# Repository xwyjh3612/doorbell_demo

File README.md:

# ESP32 4G 语音对讲

当前主板按A18外壳继续[两层语音对讲主板设计](hardware/voice_mainboard_v8_a18/README.md)，保留RGB指示灯、呼叫键、可选生命体征接口、4针TTL和USB预留。正在收尾的布线候选见[最新候选预览](hardware/voice_mainboard_v8_a18/routing_candidate/exports/preview.html)与[候选审查记录](hardware/voice_mainboard_v8_a18/routing_candidate/设计审查记录.md)；[其他工程预览入口](hardware/voice_mainboard_v8_a18/exports/preview.html)保留供比较。尚未生产放行，未连接、DRC和电源线宽以同版PCB的原生报告为准；V7及下文V6/V5费用保留为历史方案。四层工程保留作对照。

本项目是基于 ESP32-S3 + ML307 4G 的双向实时语音对讲系统。ESP32 使用 MQTT，安卓 App 和浏览器使用 WebSocket/WSS，`audio_server` Spring Boot 服务在两者之间转发 WebRTC 信令。双方通过 WebRTC/UDP/TURN 进行 Opus 16kHz 单声道语音对讲，信令服务不承载音频编解码。

独立安卓 App 支持呼叫、接听、拒接、挂断和麦克风控制，在线下载与现场操作见 [安卓演示说明.md](安卓演示说明.md)。演示入口：[https://voice.2811.top/demo.html](https://voice.2811.top/demo.html)。

0.9 版可在「设置 → 来电权限」开启后台弹窗。在其他 App 内也能看到来电页，通知与锁屏仍可直接接听。

0.8 版在首页和锁屏来电页显示动态听筒；呼出预警按日期呈现，可查看今天或近 7 天的记录。

0.7 版支持演示设备多手机接听：各手机安装并打开 App 即可同时收到来电。先接听的手机通话，其余手机停铃并显示接听者名称。设置中可把自动生成的本机名称改成“前台”或“调度室”。[呼出预警与并发呼叫说明](呼出预警与多路呼叫验证.md)

0.5版加入随无人、静止、活动变化的感知动效，以及按日期查看的状态时间线。历史由独立语音服务器保存30天，记录规则见[感知时间线与历史记录.md](感知时间线与历史记录.md)。同时移除App可恢复音频中断的8秒自动挂断，测试范围见[安卓音频恢复验证.md](安卓音频恢复验证.md)。

新增 [语音对讲 V6 集成 UPS 主板](hardware/voice_mainboard_v6/README.md)：真实充电、保护、升压与电源切换电路替换 V5 的接口预留，加入 ESP32 供电来源、电池电压和估算电量检测。新主板固件选项默认关闭，待机独立上报电源状态，App 已加入显示；[最新原生 PCB 预览与检查](hardware/voice_mainboard_v6/exports/review.html)如实列出剩余工作，尚未生产放行。以下 V5 价格与检查保留为历史方案，不能用于新 V6 下单。

当前降本设计见 [语音对讲V5主板](hardware/voice_mainboard_v5/README.md)：按用户确认的UPS输出稳压5V设计后级，ESP32-S3-WROOM-1-N8R8＋ML307C-DL直接贴板，100×75mm双层、单面SMT，圆口接5V/2A适配器。5V直接供I2S功放及可选雷达，分别降压给ESP32与4G模组，保留电量采样、BOOT接听及TTL四针。UPS内部芯片尚未确定，板上预留区域和六个焊线孔是电气接口，不能作为真实UPS芯片封装投产。本版材料＋UPS5元额度约44.09元，含PCB/加工/测试预算约52.59元/台；低价SIM座精确焊盘与器件验收完成后条件预算约50.69元/台。详见[当前逐项BOM和费用](hardware/voice_mainboard_v5/cost/费用说明.md)，均为1000台预算，非嘉立创工厂整单报价，不含电池和外设。[最新检查记录](hardware/voice_mainboard_v5/exports/validation.json)与实物验收边界随工程保存；尚未生产放行。此前[V4完整分立电源方案](hardware/voice_mainboard_v4/README.md)保留供对照。

此前的 [首批5台分阶段实施方案](首批5台分阶段实施方案.md)采用完整开发板和现有模块，先做直供电装盒演示，基础物料预算约565元。历史直供电预算不包含本轮集成主板设计。

硬约束仍是**基础语音款所有零件量产成本≤80元**。此前评估的[7元UPS模块及主板集成成本](7元UPS模块集成成本与80元整机目标.md)及100台4～6元电源目标不代表当前V3板的实际价格。V3选择了具体电源芯片并形成BOM，当前架构未达到80元目标；电量继续采用ESP32 ADC粗估，整机量产预算应包含电池、外壳、适配器等全部物料。

本轮[UPS板公开零件价格](7元UPS板公开零件价格核查.md)已列SL1045及同类电感/MOS/阻容的实际阶梯价。照片无法确认两颗主IC和完整BOM，因此尚无原板全物料公开成本合计；同类参考价格不直接作为原板替换采购料号。

完整产品需求、结构/PCB协同设计、软件运维和生产交付见 [从样机到小批销售和量产的完整路线](语音对讲产品从样机到量产路线.md)。开发板演示不能替代后续新PCB和批次工艺验证。

设备呼入使用双短电话铃，呼出使用回铃音；MQTT 联网后播放中文“联网成功”。音频素材与重新生成方法见 [提示音说明](main/call-tones.md)。

长期外接电源、偶尔断电由小电池接管的电源模块选型与接线见 [长期插电与备用电源](长期插电与备用电源.md)，包含 5V I2S 功放负载。

此前的四层模块版见 [语音对讲V3：ML307R-DL贴板与板载UPS](hardware/voice_mainboard_v3/README.md)。其[5/100/1000片费用](hardware/voice_mainboard_v3/cost/费用说明.md)及[可修改Excel](outputs/voice-v3-20261122/语音对讲V3主板费用.xlsx)保留为历史资料；1000片总成预算约125元/台包括外接开发板/模块，不是当前V5主板报价。V2/V3/V4及更早方案保留可追溯记录，后续降本以V5原生工程、实际BOM和新的1000台费用范围为依据。

本批现有手工样机的[40轮实机测试](tests/at_recovery_batch_20261121.md)已完成：33轮各自满半小时、7轮失败，电脑监督器中断1轮排除并补测；另在挂断阶段捕获ESP异常。官方协议、主动丢旧包策略及本批镜像未因PCB设计更改，旧样机结果不代表新板验收。

此前已画出 [可编辑原理图与PCB元件摆放草图](hardware/voice_carrier_v1/README.md)，保留可选生命体征雷达接口；PCB尚未布线，外壳及模块实物尺寸待核对。[带定制底板和备用电池的5台与100台预算](首版5台与100台成本.md)分别约1000元、1.39万元，属于后续候选配置，尚未取得完整供应商报价，不是当前直供电5台的采购预算。

后续评估定制备用电源底板时可参考 [此前采购与贴片清单、电路图和询价说明](outputs/first5-supplier/首批5台采购与商家询价.md)：底板每块42个SMT元件、13个插件，现有模块另外组装。当前5台直供电阶段不用这份底板BOM下单，后续设计与验证完成后再发布生产文件。

以现有约60元语音硬件为基准，备用小电池、电源管理、外壳和定制主板的增量预算，以及可选生命体征检测清单，参阅 [硬件清单与成本预算.md](硬件清单与成本预算.md)。

先用现有开发板制作带外壳和面板按钮的演示样机，选型、采购搜索入口及GPIO接线参阅 [演示样机外壳与按钮.md](演示样机外壳与按钮.md)。

## 协议约束

**ESP32 现有协议和官方 WebRTC/peer 组件保持不变。兼容转换在 Java 服务端完成。**

| 消息 | ESP32 上行字段 | ESP32 下行字段 | 浏览器常用字段 |
| --- | --- | --- | --- |
| `offer` / `answer` | `data` | `data` | `sdp` |
| `candidate` | `data` | `candidate` | `candidate` |
| `version_report` | `version` 为字符串 | — | 服务端转为整数 |
| `ota` | — | `url`、数字 `version`、可选 `md5` | 服务端配置 |

Java `SignalingMessage.normalizeMediaFields()` 补齐两种媒体字段，不改变设备使用的字段。因此默认 `index.html` 和 `index2.html` 均可使用。

## 当前通话行为

- 本地挂断只关闭媒体连接，保留 MQTT 信令实例，允许下一次呼叫。
- 只有主叫且已经成功接通过一次，异常断开后才自动重拨。等待 1500ms，最多重试三次；重拨连接失败或超时会继续剩余尝试。
- 等待重拨时状态为 `RECONNECTING`，可以主动挂断取消。对端明确 `bye` / `reject` / `timeout` 结束通话，不触发重拨。
- 呼出及接听后的连接超时使用 NVS 配置 `call_timeout`，默认 120 秒；0 或超过 3600 秒的旧配置回退为 120 秒。收到 answer 后仍等待实际 WebRTC connected，避免卡在连接中。
- 固定 `call_control` 任务串行处理命令、框架事件和截止时间。框架回调只入队，不在 peer 自身线程中等待关闭 peer。
- 固定 `mqtt_messages` 任务按接收顺序处理下行消息，避免每条消息创建临时任务。队列容量分别为 24 和 16；队列满时记录错误。
- 设备接听过来电后再次呼出，先更新缓存 ICE 的主叫角色，再启动媒体连接，避免交替呼叫时沿用上一通的被叫角色。

## OTA

仅在空闲状态启动升级，升级期间禁止新呼叫。URL 与 MD5 在创建下载任务前检查。MD5 缺失或为空时保持现有升级行为；提供 32 位十六进制 MD5 时，在接收数据期间计算，下载完成后比对。校验失败不会切换启动分区，并释放 OTA 写入句柄。

## 构建与测试

雷达检测为编译时可选，默认关闭。运行`./tools/build-firmware.ps1 -Variant voice`生成基础语音版，`-Variant voice-radar`生成24G感应版，`-Variant voice-radar60`生成60GHz呼吸/心率版；关闭时不编译雷达模块和入口。App 0.4支持后台及锁屏接听、感知数据及实际数值趋势，通话期间暂停网络上传、继续本地雷达接收。接线、配置开关和验证说明见[可选雷达固件.md](可选雷达固件.md)。

恢复以前的整套联调环境，参阅 [测试环境恢复.md](测试环境恢复.md)。在项目根目录运行 `./audio_server/start-test.ps1` 可启动本机 Java 服务。

R24D 人体感应雷达的独立读取 demo 见 [examples/radar_uart_demo/README.md](examples/radar_uart_demo/README.md)，实测记录见 [TEST_RESULTS.md](examples/radar_uart_demo/TEST_RESULTS.md)。使用 UART2、TX=GPIO8、RX=GPIO5，不改动主程序的通话协议。

换到开发板丝印TX/RX后的独立诊断程序见 [examples/radar_pin_demo/README.md](examples/radar_pin_demo/README.md)。当前`rx44-1`版使用原生USB控制台，UART2默认GPIO44/115200只接收，运行时可切换GPIO43/44/5与波特率；接GPIO44需隔离板载CH343发送端，GPIO43替代测试需在程序启动并切换配置后才接入。

雷达改回GPIO5/8并使用CH343 UART口（本机COM13）的独立测试版见 [examples/radar_gpio5_demo/README.md](examples/radar_gpio5_demo/README.md)。当前`rx5-uart-2`默认GPIO5/115200接收，支持GPIO6/8切换，保存最近512字节；GPIO8不作为发送输出，重启恢复GPIO5。两个demo的控制台接口不同，采集脚本会检查设备及运行程序。

GPIO6持续采集与实时监测页面见 [examples/radar_monitor/README.md](examples/radar_monitor/README.md)，本机地址为 [http://127.0.0.1:18888](http://127.0.0.1:18888)。已验证GPIO6/115200的有效初始化及多次有人/无人上报，页面区分历史数据、新报文及设备串口连接状态。

新接入的 R60ABD1 60GHz 呼吸睡眠雷达演示见 [examples/radar_r60abd1_demo/README.md](examples/radar_r60abd1_demo/README.md)，本机页面为 [http://127.0.0.1:18890](http://127.0.0.1:18890)。沿用 GPIO6 接收，电脑端解析呼吸、心率、体动和距离，无需替换语音固件。

固件使用 ESP-IDF 5.4.3，当前目标为 ESP32-S3、8MB Flash、PSRAM。进入已激活的 ESP-IDF 环境后运行：

```sh
idf.py build
```

服务端需要 Java 8 和 Maven：

```sh
cd audio_server
mvn test package
```

主机测试编译完整的应用源文件，仅替换平台 include 和硬件 API。OTA 测试使用 ESP-IDF 中真实的 Mbed TLS MD5 实现，模拟下载分片与分区写入：

```sh
python -m pip install --target build/host-tools ziglang
python tests/run_host_tests.py --idf /path/to/esp-idf
```

也可通过 `--compiler` 指定 clang、gcc 或 zig。脚本可从现有 `build/project_description.json` 自动读取 ESP-IDF 路径。

当前自动化覆盖 11 个通话场景（含呼入、呼出、联网提示音和 BOOT 接听保护）、8 个 OTA 场景、4 个 UDP 最新包场景、UART FIFO 回调死锁回归、雷达解析及上传保护、14 个 Java 协议/观测/路由用例，以及9个Android状态检查。UDP 测试使用实际双线程，验证主动丢旧包、读取快照完整性及 10 万次并发覆盖；改动和验证边界见 [tests/udp_receive_notes.md](tests/udp_receive_notes.md)。主机测试不验证 ML307 实际网络、音质或设备重启，需要硬件联调确认这些行为。

2026-11-20 [连续通话验收与复测](tests/real_call_validation_20261120.md)：19:06 的独立 30 分钟通话通过，901 次双向统计、零 AFE 满告警、零 AT 超时、零模组启动通知；19:52 使用同一固件再次测试，约 14 分 43 秒后 AT 超时、ML307 重新初始化，随后出现 AFE 满告警，复测失败。呼叫端为原生 App（Android 10 模拟器），对端为实物 ESP32-S3 / ML307R-DL，沿用现有手机充电器供电，雷达电源未接入。当前故障仍未排除，根因尚未确定，声音延迟未测量。

2026-11-21 [更换手机充电器及接线排查的复测](tests/real_call_validation_20261121.md)：08:50 的独立半小时通过；随后八轮已接通测试完成，四轮各自1800秒通过、四轮中断，另四次早期准备失败单列。第8轮在12:22出现发送应答超时及AFE，未捕获模组启动通知；之后新增五次呼叫都未接通，追加五轮有效通话尚待网络恢复后补足。静态检查未发现业务调用ML307重启或开启UDP透传，普通模式中的临时数据输入异常恢复仍需排查，见 [命令模式检查](tests/ml307_command_mode_review_20261121.md)。根因尚未确定，指示灯闪烁和网络已注册不证明AT/UDP通路健康；本轮未改动或重刷固件。

## 阅读入口

- `main/main.cpp`：设备初始化。
- `main/webrtc_mqtt.c`：通话控制与重拨。
- `main/mqtt_signaling.cpp`：保持现有设备协议的 MQTT 实现。
- `main/otaupgrade.cpp`：HTTP OTA、校验与资源清理。
- `audio_server/src/main/java`：WebSocket 与 MQTT 信令桥接。
- `MAIN系统功能梳理.md`、`MQTT信令简要说明.md`、`audio_server/AI_PROJECT_GUIDE.md`：详细模块说明。

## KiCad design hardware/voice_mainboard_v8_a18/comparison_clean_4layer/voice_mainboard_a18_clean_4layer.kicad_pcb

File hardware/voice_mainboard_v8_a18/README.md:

# 语音对讲主板：A18外壳适配工程

本工程是独立的A18适配工作版，保留V7原工程。**当前尚未生产放行，不能据预览图下单。** 当前选择两层，正在收尾的PCB位于 [power_relayout_candidate](power_relayout_candidate/voice_mainboard_a18_2layer.kicad_pcb)。完成同版检查后，报告与预览写入该目录的 `exports`，不能使用旧候选报告代替它。`two_layer_work`、`routing_candidate`、`signal_relayout_candidate`保留为此前工作版本。历史试排和布线试验的报告不代表当前PCB。

2026-11-27更新：**当前两层PCB的铜线连接已经完成**，USB D+和功放数据线均已接通。当前PCB SHA256为 `4c907236ab2557cdb0d9d4e8ab16a466c671240d4630f1b35d93b14c43e0c42f`，同版ERC、DRC、未连接及原理图一致性均为0。圆口插座和喇叭针座已调整位置；电源入口改为约5mm长、0.8mm宽的路径，铜线估算2A压降约0.0083V。89段电源铜线经过逐网原生检查后加宽至0.8mm。该估算不代表2A瞬态或温升合格。

已导出 [打样资料审查包](prototype_review_20261127.zip)，包含同版Gerber、钻孔/槽孔、物料、贴装坐标、可编辑工程、原理图PDF、现有STEP模型与检查记录。它仍是审查版：USB差分/支路走法、采购料号与关键封装、外壳实物尺寸、电源及电池动态验证尚未闭环。详细状态见 [设计完成度与交付](设计完成度与交付.md)。不能把“布线全部接通”表述为“已经完成生产放行”。

2026-11-26更新：从 [预览入口](exports/preview.html) 查看各工程的真实状态。原两层工作工程、两层对照和四层供电优化对照均保留；按用户选择继续两层。新版调整4G供电与电平转换、复位、SIM、功放和升压区域，再补齐连接；具体剩余问题见当前两层报告。四层对照的ERC、DRC、未连接、原理图一致性问题均为0，属于历史对照，不能用它的报告替两层放行。

最新PCB是 [两层供电重排候选](power_relayout_candidate/voice_mainboard_a18_2layer.kicad_pcb)。电源切换芯片移到升压与功放附近，优先保留主供电及地回流路径，再修复信号连接。候选独立核查所有电源铜线宽度；能够安全加宽的线路逐网通过原生DRC验证后保留。升压开关线采用芯片与电感附近的局部走法。铜路径估算不含芯片、电感、连接器、电池内阻和温升，不能代表整机2A已实测合格。

已生成四层对照的板体STEP及含可用模型STEP；150个封装中121个找到可显示的模型，29个没有模型，其中包括ML307C、SIM座、电源口及部分电源/音频芯片。详见 [模型清单](comparison_clean_4layer/exports/model-inventory.json)。缺失模型不能作为装壳无碰撞的依据。打样前具体待办见 [工程审查记录](comparison_clean_4layer/设计审查记录.md)。

板外包73×73mm，按图中1.20标注设定板厚1.2mm，四个Ø3mm安装孔的孔距为66×66mm；下方36mm宽缺口避让电池仓。正面限高10mm，背面限高15mm。采用两层板、双面贴装；原470µF电容C8移至背面，保持原封装和电气值。中央保留呼叫键，上部保留RGB灯，可选生命体征接口、四针TTL和USB接口保留。

RGB灯供电已从ESP电源改接稳压3.8V：厂家给出的VDD范围为3.3～5.3V，ESP供电的计算低角值约3.21V，原接法存在低压边界风险。3.8V电源的反馈容差范围约3.745～3.872V；厂家VIH=0.55×VDD，与ESP GPIO电平兼容。这是静态范围修正，仍需要新板动态/灯色实测。

## 实际检查与仿真范围

2026-11-27已新增实际ngspice上电运算，报告见 [上电仿真报告](power_relayout_candidate/exports/powerup-simulation-20261127/上电仿真报告.html)，波形、每项输入网表、日志及结果见 [仿真资料包](上电仿真资料-20261127.zip)。该报告与当前PCB SHA256对应；没有修改固件或PCB。

新增37个场景中29项在所声明模型内通过、4项在保守压力条件下失败、3项因求解中止或TI模型功能缺失未得结论，1项保留NTC短路禁用温度检测的已知限制。TI TPS2117使用未改动的官方Final1.10瞬态模型，SY8089降压采用平均控制近似并使用当前PCB反馈值、已贴装电容和铜线电阻。另列工程切换间隔扫描；它不是官方模型。完整拔外电时进入的二极管模式不在该TI模型覆盖范围，实际ETA1096升压和化学电芯也没有得到验证。

用户更新测得约0.7A；测量位置和仪表带宽未知，仿真单列模组3.8V端0.7A/0.8A负载。5V输入、0.7A模组基础负载下，模组最低约3.75V；叠加假定2A、500µs脉冲后约3.54V，在模型内高于3.4V下限。4.5V输入、0.2A基础负载、假定2A脉冲的20/50/100µs工程模型通过，500µs工程模型约3.26V而失败；5V输入、500µs的TI切换组合模型通过。脉冲宽度是扫描假设，厂家仅说明2A瞬态，并未给出宽度，不能把2ms压力场景当作实测持续通话电流或据此断定2A输入不足。

电池ADC真实R/C网络时间常数约6ms，GPIO打开采样后等待约40ms可接近0.4倍电芯电压。该结论来自真实RC运算；GPIO采样时序尚需在新板固件实现，当前通话测试固件未修改。U16物料注释已更正为实际R64=12k、100mA，未改变器件或线路。

- 从保存的PCB读出435个已分配网络的引脚，与原理图XML网表逐一比对；检查输入极性、3.3V/1.8V串口方向、PSRAM保留GPIO、喇叭桥接输出、电池保护负极和电源来源/电量监测引脚。网表一致不代表PCB走线已经连通。
- 运行原生KiCad ERC、DRC、原理图一致性与未连接检查。检查错误必须修复，不能删除有问题的引脚或添加排除项掩盖错误；设计规则要对应所选加工工艺并记录依据。
- 运行ngspice四组分压/理想CE开关模型：25℃、−5℃、45℃、NTC开路。充电设定改为100mA；NTC暂按10k/B3950，低温名义门限调整为约3.3℃，高温约40.5℃。电芯和实际NTC未冻结，尚不能判定真实电池已合格。
- 运行12组被动储能瞬态模型：输入4.5V、2A负载，扫描电容有效容量和理想电源中断时间。包含C8、假定ESR及线路电阻，并检查模型确实施加了2A负载。结果是敏感性分析，不是TPS2117或升降压芯片内部动态仿真。
- ML307C的3.8V供电保留C6/C7，并按硬件手册补两颗220µF的C75/C76（APAQ 6R3AVEA221M0645，C176322）。两颗电容约4.3mm高，装在背面；焊盘和极性需确认实物。对比8组有／无这两颗电容的局部储能模型；报告列出供电中断假设、实际铜线估算和VBAT最低电压。SY8089带新增电容的启动和环路仍需实测。
- 使用资料中的反馈基准范围与实际电阻做三路电源工作点容差计算。名义值分别约3.809V、3.315V、4.992V；不包含负载、温度和PCB寄生造成的动态压降。

**没有模拟ESP32/ML307的内部执行、蜂窝网络、射频匹配、音频质量、化学电芯充放电或完整整板热行为，也没有实际新主板上电记录。ERC/DRC为零也不能代替这些验证。** ESP32官方通信协议及音频主动丢旧包策略未因本次CAD工作改动。

## 已明确的电源行为

外电路径为输入保险丝/反接保护→TPS2117外电输入→系统5V→4G和ESP降压；电池不串在外电供电路径上。因此拓扑支持不安装电池、只用外电，但仍需样板验证冷启动和4G负载。

电池为单节4.2V体系锂离子/锂聚合物，接口依次为BAT+、CELL_NEG、NTC。**CELL_NEG是原始电池负极，不能短接到系统GND，否则会绕过保护。** NTC线也不能短接到地来关闭温度检查；该芯片的TEMP短路可能禁用温度监测，开路暂停测试不证明短路受保护。

5V输出峰值2A时，低电量电池的平均放电电流可能超过4A；小容量电池是否支持这一脉冲必须查实际电芯规格。ETA1096在30kΩ电流设定下只给出典型限流值，不能把典型值当作保证下限。主板要实测低电量、入网/发射峰值、电源切换和温升。

GPIO38经Q7可暂停充电。**80%停充/70%恢复的电量迟滞尚未实现。** 当前硬件默认按充电芯片的4.2V规则充电；电压估算SOC、无电池识别及启动策略需后续实现与实际电芯校准。

模组硬件复位路径为ESP32 GPIO21→Q2开漏→ML307C RESET_N，保留R8栅极下拉和C19滤波。它不依赖模组能够回复AT指令。当前开发板没有接这条线，因此此次主板设计不能让现有开发板突然具备硬复位能力；主板样件还需验证复位脉宽与模块恢复流程。四层对照该线当前铜路径估算约24.6mm，需按模组手册的短走线建议继续审核与调整。

## 预览和机械验证

最新的 [3D四视图](power_relayout_candidate/exports/3d-preview-20261127/语音对讲主板-3D四视图.png) 和 [3D原图查看页](power_relayout_candidate/exports/3d-preview-20261127/index.html) 包含贴件/裸板的正背面图，完整图片见 [3D图片包](语音对讲主板-3D图片-20261127.zip)。使用当前PCB的隔离渲染副本，不修改源PCB。按默认贴装显示，DNP选装件隐藏；4G模组、圆口和部分芯片为简化外形或通用封装示意，蓝绿色为渲染配色。详细范围见图片目录内的模型说明，不能据示意外形完成装壳无碰撞核准。

完成当前检查导出后，用浏览器打开 `exports/preview.html` 查看正背面、真实仿真波形和检查记录。`exports/mechanical-1to1.svg` 按100%打印，关闭适应页面，先量50mm标尺，再核对外壳。

截图足以建立候选外形，但螺柱外径、上缺口的精确解释、局部按钮/导光柱行程、仓内电芯尺寸、喇叭/麦克风和插头弯线空间仍需厂家尺寸图或实物验证。已有模型的STEP仅用于CAD查看；缺失模型的元件依然存在，不能据空白位置判断没有碰撞。

TTL接口是GND、ESP TX43、ESP RX44、5V输入。串口逻辑为3.3V；四针中的5V是供电，不能据此将TX/RX配置为5V逻辑。已有外电时不要直接把另一电源的5V并接进来。喇叭接SPK+和SPK−，两端均不是GND。

## 打样前仍需闭环

模组底部LGA与功放密集引脚使用0.45mm焊环/0.20mm孔的普通过孔、0.16mm短引脚颈线，保持0.20mm铜间距及0.10mm最小环宽；不是激光微孔或默认填孔的盘中孔。电源主干采用较大过孔及较宽走线。原工程0.30mm最小孔径/0.50mm最小过孔是原先的保守工艺选择；这里按公开工艺能力调整为0.20/0.45mm，用于密集封装引出，并继续做独立DRC。依据为[嘉立创海外站公开PCB能力](https://jlcpcb.com/capabilities/pcb-capabilities)，其推荐最小过孔孔径为0.20mm，0.20mm孔且焊环直径小于0.45mm会增加费用。国内嘉立创具体下单价格尚未获取，不能据此宣称打样费不变。

最终保存PCB应同时满足ERC、DRC、未连接和原理图一致性检查，并核查所有大电流路径、短窄引脚颈线、普通过孔承流、开关电源回路、地参考、射频及USB走线。L5已按顺络目录选为SWPA4030S2R2NT，2.2µH、DCR最大0.039Ω，厂家建议焊盘与现有4030封装相符，依据见[选型记录](power_relayout_candidate/exports/l5-part-selection.json)。嘉立创采购编号和实际库存尚未核实；部分关键封装的供应商确认和实际外设尺寸仍需冻结。

首次样板按限流上电→无电池外电启动→三路电压→4G入网/通话负载→断电切换→低电量/温度充电暂停→长通话验证的顺序测量；示波器记录模块脚处瞬态电压，不能仅用万用表平均值判断发射峰值供电。

## 重现检查

在项目根目录运行 `hardware/voice_mainboard_v8_a18/review_two_layer_work.ps1 -Board hardware/voice_mainboard_v8_a18/power_relayout_candidate/voice_mainboard_a18_2layer.kicad_pcb -Export3D`，导出指定两层工程的网表、ERC、DRC、切换／充电／VBAT局部模型、铜路径估算、正背面预览和已有模型STEP。该脚本以只读模式运行充电控制核查，应在该版本停止布线写入后运行。

检查结果只写入所指定的候选目录，包含实际电源线宽审查；不会覆盖旧工作版或将候选自动标记为可生产。

`audit_electrical.py` 是只读电气/网表检查和被动模型仿真；`audit_controls.py` 默认会同步固定电阻设定，手动运行时应使用 `A18_AUDIT_READ_ONLY=1`，不能在其他脚本布线时并发修改工程。以下命令为原两层历史工程检查示例：

```powershell
& build/cad-tools/kicad/bin/kicad-cli.exe sch export netlist --format kicadxml --output hardware/voice_mainboard_v8_a18/exports/netlist.xml hardware/voice_mainboard_v8_a18/voice_mainboard_v8_a18.kicad_sch
& build/cad-tools/kicad/bin/python.exe hardware/voice_mainboard_v8_a18/audit_electrical.py
& build/cad-tools/kicad/bin/kicad-cli.exe pcb drc --format json --schematic-parity --output hardware/voice_mainboard_v8_a18/exports/review-drc.json hardware/voice_mainboard_v8_a18/voice_mainboard_v8_a18.kicad_pcb
```

`create_layout.py`、`prepare_completion.py` 和各布线脚本是版本构建/修改工具，不能在已有成品路径上随意重跑。历史快照仅用于恢复和比较，不是另一套可同时下单的主板。

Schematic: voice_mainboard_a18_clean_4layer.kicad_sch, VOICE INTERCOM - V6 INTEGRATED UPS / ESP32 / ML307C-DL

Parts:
C4, C6, C7, C59, C60: 22u 16V; C_0805_2012Metric
C5: 22u 16V; C_0805_2012Metric; not fitted
C8: OCV471M1ATR-1010 470u 10V; CP_Elec_10x10.5
C10: 10u 10V; C_0805_2012Metric
C11, C13, C14, C15, C16, C17, C18, C58, C62, C69, C70: 100n; C_0603_1608Metric
C12: 33p; C_0603_1608Metric
C19, C29: CL10B103KB8NNNC; C_0603_1608Metric
C20, C28: CL10B104KB8NNNC C1591; C_0603_1608Metric
C24, C25: RF MATCH SHUNT DNP; C_0603_1608Metric; not fitted
C26: 100n MIC; C_0603_1608Metric
C37: 22p MODEM CFF; C_0603_1608Metric
C56: 1u EN delay; C_0603_1608Metric
C57: 22u; C_0805_2012Metric
C61: 10u; C_0805_2012Metric
C63: 22p ESP CFF; C_0603_1608Metric
C64, C65, C66, C71, C72, C73: 22u 10V X5R; C_0805_2012Metric
C67, C68: 10u 10V X5R; C_0805_2012Metric
C74: 100n RGB; C_0603_1608Metric
D1: SRV05-4 MSKSEMI; SOT-23-6
D2: WS2812B-2020-V6; LED_WS2812B-2020_PLCC4_2.0x2.0mm
F1: ASMD1812-400-16V C55014590; Fuse_1812_4532Metric
J1: HX DC005-2.5-T 3A C18357600; HX_DC005_2p5_T
J8: MODEM DOWNLOAD STRAP OPEN NORMAL; PinHeader_1x02_P2.54mm_Vertical; not fitted
J10: JAE SF72S006 SIM CANDIDATE; JAE_SIM_Card_SF72S006
J11: LTE ANT U.FL; UFL_Hirose_Active4Layer_A18
J12: MODEM USB SERVICE VBUS DM DP GND; PinHeader_1x04_P2.54mm_Vertical; not fitted
J14: INMP441 MODULE 3V3 GND BCLK WS SD; PinHeader_1x05_P2.54mm_Vertical
J15: SPEAKER BTL + / - NEVER GND; PinHeader_1x02_P2.54mm_Vertical
J16: OPTIONAL RADAR 5V GND RX6 TX8; PinHeader_1x04_P2.54mm_Vertical
J17: EXTERNAL CALL BUTTON; PinHeader_1x02_P2.54mm_Vertical
J18: TTL GND TX43 RX44 5V; PinHeader_1x04_P2.54mm_Vertical
J22: USB HOST RESERVE GND DP20 DM19; PinHeader_1x03_P2.54mm_Vertical; not fitted
J23: 1S CELL + / - / NTC; PinHeader_1x03_P2.54mm_Vertical
L1: SWPA6045S2R2MT C83455; L_Sunlord_SWPA6045S
L4: SWPA6045S2R2MT; L_Sunlord_SWPA6045S
L5: 2.2uH SWPA4030S 3A TARGET; L_Sunlord_SWPA4030S
Q1, Q2, Q4, Q5: 2N7002K-7 C85047; SOT-23
Q3: BSS84,215 C493579; SOT-23
Q6: DMP2035U-7 C110499; SOT-23
Q7: 2N7002K-7; SOT-23
R2: 100k 0.1% MODEM RH; R_0603_1608Metric
R3: 18.7k 0.1% MODEM RL; R_0603_1608Metric
R4, R12, R21, R68, R72, R73, R74: 10k; R_0603_1608Metric
R5, R6, R8, R15, R16, R32, R69: 100k; R_0603_1608Metric
R7: 4.7k AUTO ON DNP; R_0603_1608Metric; not fitted
R9, R10, R11: 22R; R_0603_1608Metric
R13: 0R RF SERIES; R_0603_1608Metric
R14: 10k BOOT; R_0603_1608Metric
R17: 150k 1%; R_0603_1608Metric
R18, R20: 100k 1%; R_0603_1608Metric
R19: 10k 1%; R_0603_1608Metric
R26: 0R USB SERVICE DP; R_0402_1005Metric
R27: 0R USB SERVICE DM; R_0402_1005Metric
R28: 0R USB HOST DP; R_0402_1005Metric; not fitted
R29: 0R USB HOST DM; R_0402_1005Metric; not fitted
R30: 0R VBUS FROM SERVICE; R_0603_1608Metric
R31: 0R VBUS DETECT FROM SYSTEM DNP; R_0603_1608Metric; not fitted
R57: 10k EN; R_0603_1608Metric
R58: 0R RADAR POWER OPTIONAL; R_0603_1608Metric; not fitted
R59: 100k 1% RH ESP; R_0603_1608Metric
R60: 22.1k 1% RL ESP; R_0603_1608Metric
R61: 73.2k 0.1%; R_0603_1608Metric
R62: 10k 0.1%; R_0603_1608Metric
R63: 30k 1% ISET; R_0603_1608Metric
R64: 12k 1%; R_0603_1608Metric
R65: 6.19k 1% NTC TOP; R_0603_1608Metric
R66: 200k 1%; R_0603_1608Metric
R67: 0R NTC LINK; R_0603_1608Metric
R70: 100k 0.1% PR TOP; R_0603_1608Metric
R71: 33.2k 0.1% PR BOTTOM; R_0603_1608Metric
R75: 0R LEFT CHANNEL; R_0603_1608Metric
R76: 0R 12dB; R_0603_1608Metric
R77: 330R RGB DIN; R_0603_1608Metric
SW1, SW2, SW3: TACT 4.5x4.5 SMD; SW_SPST_TL3342
TP1: POWER_BUS; V6_BOARD_TP1
TP2: MODEM_STATE_1V8; V6_BOARD_TP2
TP3: MODEM_NETLIGHT; V6_BOARD_TP3
TP4: DEBUG_ESP_TX43; V6_BOARD_TP4
TP5: DEBUG_ESP_RX44; V6_BOARD_TP5
TP6: GND; V6_BOARD_TP6
TP7: VIN_PROTECTED; V6_BOARD_TP7
TP8: POWER_BUS; V6_BOARD_TP8
TP9: SYS_5V UPS OUTPUT TEST; V6_BOARD_TP9
TP10: ESP_3V3; V6_BOARD_TP10
TP12: MUX ST / GPIO47; V6_BOARD_TP12
TP13: BAT BOOST 5V; V6_BOARD_TP13
TP14: CELL NEG isolated; V6_BOARD_TP14
TP15: DBG_TX_1V8; V6_BOARD_TP15
TP16: DBG_RX_1V8; V6_BOARD_TP16
TP17: MODEM_1V8; V6_BOARD_TP17
U1: ML307C-DL; ML307C_DL_109_LIBRARY_REVIEW
U2, U13: SY8089A1AAC; SOT-23-5
U3, U4, U5: SN74LVC1T45DBVR; SOT-23-6
U7: ESP32-S3-WROOM-1-N8R8; V6_U7_SMD_LAND_MATCH
U14: MAX98357AETE+; V6_U14_SMD_LAND_MATCH
U15: ETA1096E8A; ETA1096_ESOP8
U16: TP4056-MS; SOIC-8-1EP_3.9x4.9mm_P1.27mm_EP2.29x3mm
U17: XB7608AJL; XB7608_CPC5
U18: TPS2117DRLR; TI_DRL0008A
U19: ME2807A30M3G; SOT-23

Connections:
AMP_GAIN: R76.1, U14.2
AMP_SD: R75.2, U14.4
BAT_ADC2: C28.1, R17.2, R18.1, U7.38
BAT_ADC_EN9: Q4.1 (G), R16.1, U7.17
BAT_BOOST_5V: C65.1, C66.1, C73.1, R61.1, TP13.1, U15.7 (OUT), U18.6 (VIN2)
BAT_DIV_SW: Q3.3 (D), R17.1
BAT_GATE: Q3.1 (G), Q4.3 (D), R15.2
BAT_SENSE_IN: C64.1, C68.1, C69.1, C70.1, J23.1, L4.1, Q3.2 (S), R15.1, U15.4 (IN), U16.5 (BAT), U17.1 (VDD), U19.3 (VIN)
BAT_TEMP: R65.2, R66.1, R67.2, U16.1 (TEMP)
BOOST_EN: U15.2 (EN), U19.1 (RESET_N)
BUCK_FB: C37.2, R2.2, R3.1, U2.5 (FB)
BUCK_SW: L1.1, U2.3 (LX)
CALL_BOOT0: J17.1, R14.2, SW1.1, U7.27
CELL_NEG: C69.2, J23.2, TP14.1, U17.2 (CELL_GND), U17.3 (CELL_GND)
CELL_NTC: J23.3, R67.1
CHG_ACTIVE_N: R73.2, U7.25 (IO48), U16.7 (CHRG)
CHG_CE: Q7.3 (D), R68.2, U16.8 (CE)
CHG_DISABLE_IO38: Q7.1 (G), R69.1, U7.31 (IO38)
CHG_FULL_N: R74.2, U7.39 (IO1), U16.6 (STDBY)
CHG_PROG: R64.1, U16.2 (PROG)
DBG_RX_1V8: TP16.1, U1.38 (DBG_RXD)
DBG_TX_1V8: TP15.1, U1.39 (DBG_TXD)
DEBUG_ESP_RX44: J18.3, TP5.1, U7.36
DEBUG_ESP_TX43: J18.2, TP4.1, U7.37
ESP_3V3: C13.1, C15.1, C17.1, C26.1, C57.1, C58.1, C60.1, C63.1, J14.1, L5.2, R4.1, R14.1, R21.1, R57.1, R59.1, R72.1, R73.1, R74.1, TP10.1, U3.1 (VCCA), U3.5 (DIR), U4.1 (VCCA), U5.1 (VCCA), U5.5 (DIR), U7.2 (3V3)
ESP_DTR4: R5.1, U5.3 (A), U7.4
ESP_EN: C56.1, R57.2, SW2.1, U7.3 (EN)
ESP_FB: C63.2, R59.2, R60.1, U13.5 (FB)
ESP_RX18: U4.3 (A), U7.11
ESP_SW: L5.1, U13.3 (SW)
ESP_TX17: R4.2, U3.3 (A), U7.10
ESP_USB_DM19: J22.3, R29.2, U7.13
ESP_USB_DP20: J22.2, R28.2, U7.14
EXT_DETECT_GATE: C29.1, Q5.1 (G), R19.2, R20.1
EXT_PRESENT_N_IO10: Q5.3 (D), R21.2, U7.18
GND: C4.2, C5.2, C6.2, C7.2, C8.2, C10.2, C11.2, C12.2, C13.2, C14.2, C15.2, C16.2, C17.2, C18.2, C19.2, C20.2, C24.2, C25.2, C26.2, C28.2, C29.2, C56.2, C57.2, C58.2, C59.2, C60.2, C61.2, C62.2, C64.2, C65.2, C66.2, C67.2, C68.2, C70.2, C71.2, C72.2, C73.2, C74.2, D1.2 (GND), D2.2 (GND), J1.2 (SLEEVE_MFR2), J8.2, J10.C5 (GND), J10.CSW (DETECT_COM), J10.SH (SHIELD), J11.2, J12.4, J14.2, J16.2, J17.2, J18.1, J22.1, Q1.2 (S), Q2.2 (S), Q4.2 (S), Q5.2 (S), Q7.2 (S), R3.2, R5.2, R6.2, R7.2, R8.2, R16.2, R18.2, R20.2, R32.2, R60.2, R62.2, R63.2, R64.2, R66.2, R69.2, R71.2, R76.2, SW1.2, SW2.2, SW3.2, TP6.1, U1.1 (GND), U1.10 (GND), U1.27 (GND), U1.34 (GND), U1.36 (GND), U1.37 (GND), U1.40 (GND), U1.41 (GND), U1.45 (GND), U1.46 (GND), U1.47 (GND), U1.48 (GND), U1.70 (GND), U1.71 (GND), U1.72 (GND), U1.73 (GND), U1.88 (GND), U1.89 (GND), U1.90 (GND), U1.91 (GND), U1.92 (GND), U1.93 (GND), U1.94 (GND), U1.95 (GND), U2.2 (GND), U3.2 (GND), U4.2 (GND), U4.5 (DIR), U5.2 (GND), U7.1 (GND), U7.40 (GND), U7.41 (GND), U13.2 (GND), U14.3, U14.11, U14.15, U14.17, U15.1 (GP), U15.8 (GP), U15.9 (AGND_EP), U16.3 (GND), U16.9 (EP), U17.4 (PACK_NEG), U17.5 (PACK_NEG), U18.1 (GND), U19.2 (GND)
I2S_MIC_BCLK14: J14.3, U7.22
I2S_MIC_DATA12: J14.5, U7.20
I2S_MIC_WS13: J14.4, U7.21
I2S_SPK_BCLK15: U7.8, U14.16
I2S_SPK_DATA7: U7.7, U14.1
I2S_SPK_WS16: U7.9, U14.14
MODEM_1V8: C14.1, C16.1, C18.1, R12.1, TP17.1, U1.24 (VDD_EXT), U3.6 (VCCB), U4.6 (VCCB), U5.6 (VCCB)
MODEM_3V8: C6.1, C7.1, C10.1, C11.1, C12.1, C37.1, C74.1, D2.4 (VDD), L1.2, R2.1, TP1.1, TP8.1, U1.42 (VBAT), U1.43 (VBAT)
MODEM_BOOT_N: J8.1, U1.82 (BOOT_MODE)
MODEM_NETLIGHT: TP3.1, U1.16 (NETLIGHT)
MODEM_PWRKEY_N: Q1.3 (D), R7.1, SW3.1, U1.7 (PWR_ON/OFF)
MODEM_RESET_N: C19.1, Q2.3 (D), U1.15 (RESET)
MODEM_STATE_1V8: TP2.1, U1.25 (STATE)
M_DTR_1V8: U1.19 (UART0_DTR), U5.4 (B)
M_RX_1V8: U1.17 (UART0_RXD), U3.4 (B)
M_SIM_CLK: R10.1, U1.13 (USIM0_CLK)
M_SIM_DATA: R9.1, U1.11 (USIM0_DATA)
M_SIM_RESET: R11.1, U1.12 (USIM0_RESET)
M_TX_1V8: U1.18 (UART0_TXD), U4.4 (B)
M_USB_DM: R27.1, R29.1, U1.60 (USB_DM)
M_USB_DP: R26.1, R28.1, U1.59 (USB_DP)
PWRKEY_CTL: Q1.1 (G), R6.1, U7.19
RADAR_5V: J16.1, R58.2
RADAR_RX6: J16.3, U7.6
RADAR_TX8: J16.4, U7.12
RESET_CTL: Q2.1 (G), R8.1, U7.23
REVERSE_GATE: Q6.1 (G), R32.1
RF_ANT: C24.1, R13.1, U1.35 (ANT_MAIN)
RF_FEED: C25.1, J11.1, R13.2
RGB_LED_DIN: D2.3 (DI), R77.2
SERVICE_USB_DM: J12.2, R27.2
SERVICE_USB_DP: J12.3, R26.2
SERVICE_USB_VBUS: J12.1, R30.1
SIM_CLK: D1.3 (IO), J10.C3 (CLK), R10.2
SIM_DATA: D1.1 (IO), J10.C7 (IO), R9.2
SIM_DETECT: J10.DSW (DETECT), R12.2, U1.79 (USIM0_DET)
SIM_RESET: D1.4 (IO), J10.C2 (RST), R11.2
SIM_VCC: C20.1, D1.5 (VCC), D1.6 (IO), J10.C1 (VCC), U1.14 (USIM0_PWR)
SPK_MINUS: J15.2, U14.10
SPK_PLUS: J15.1, U14.9
STATUS_LED_IO39: R77.1, U7.32 (IO39)
SUPPLY_BAT_N47: R72.2, TP12.1, U7.24 (IO47), U18.8 (ST)
SYS_5V: C4.1, C5.1, C8.1, C59.1, C61.1, C62.1, C72.1, R31.1, R58.1, R75.1, TP9.1, U2.1 (EN), U2.4 (IN), U13.1 (EN), U13.4 (VIN), U14.7, U14.8, U18.2 (VOUT), U18.7 (VOUT_COMMON)
UPS_FB: R61.2, R62.1, U15.5 (FB)
UPS_ISET: R63.1, U15.6 (ISET)
UPS_PR1: R70.2, R71.1, U18.4 (PR1)
UPS_SW: L4.2, U15.3 (SW)
USB_DETECT_5V: R30.2, R31.2, U1.61 (USB_VBUS)
VIN_DC: F1.1, J1.4 (CENTER_PLUS_MFR4), J18.4, R19.1
VIN_FUSED: F1.2, Q6.3 (D)
VIN_PROTECTED: C67.1, C71.1, Q6.2 (S), R65.1, R68.1, R70.1, TP7.1, U16.4 (VCC), U18.3 (VIN1), U18.5 (MODE)

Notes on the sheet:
01 INPUT / MODEM 3.80856V
02 ETA1096 / CHARGE / PROTECT / MUX
03 ML307 / UART / RESET
04 SIM / RF / USB RESERVE
05 ESP / BOOT / ADC / TTL
06 ESP3.315V / I2S AUDIO
07 TEST PADS
V6: V6 UPS: ETA1096 battery boost + TPS2117 external priority; two SY8089A1 bucks; nominal5V audio/radar.
Battery J23 = CELL+ / isolated CELL- / NTC. CELL- must NOT short to systemGND; U17 is protection.
J18 TTL = GND / ESP TX43 / ESP RX44 / adapter5V. Do not parallel TTL5V and main adapter.
SIM JAE footprint retained until exact cheap socket drawing; GPIO6/8 radar; GPIO47 muxST; ADC2 with GPIO9 gate; GPIO38 charge pause; GPIO48/1 charge status.
Electrical/geometry checks do not validate load, startup, temperature, RF, USB or call function.

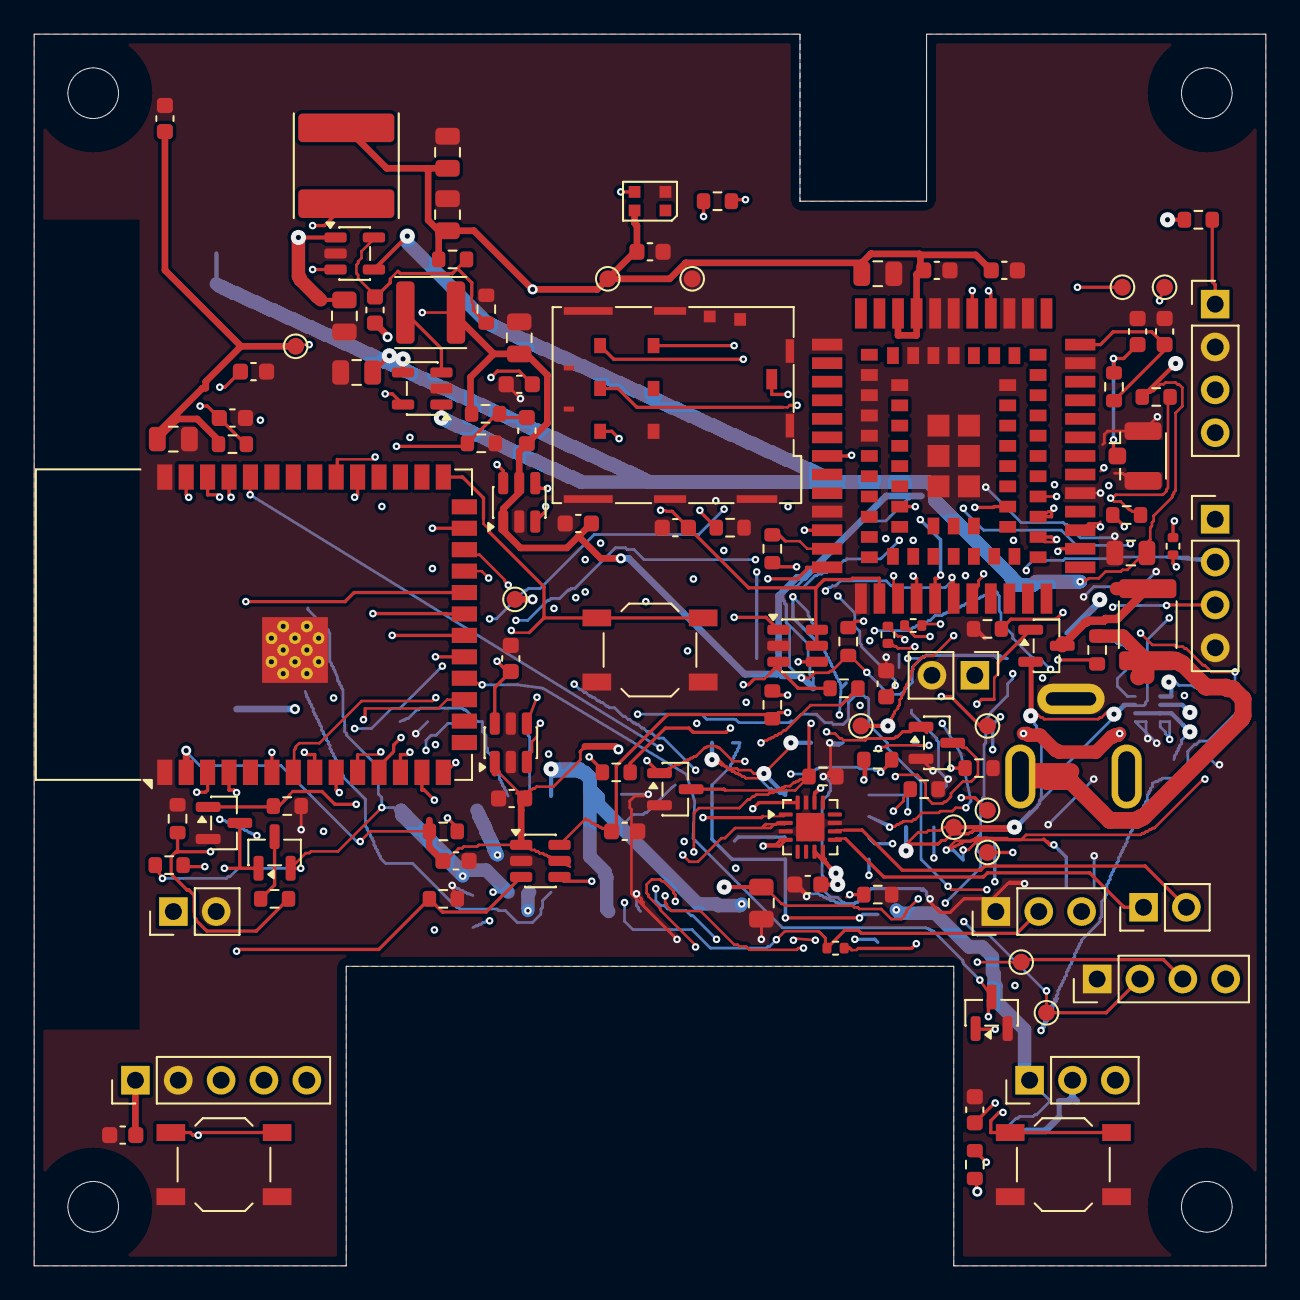
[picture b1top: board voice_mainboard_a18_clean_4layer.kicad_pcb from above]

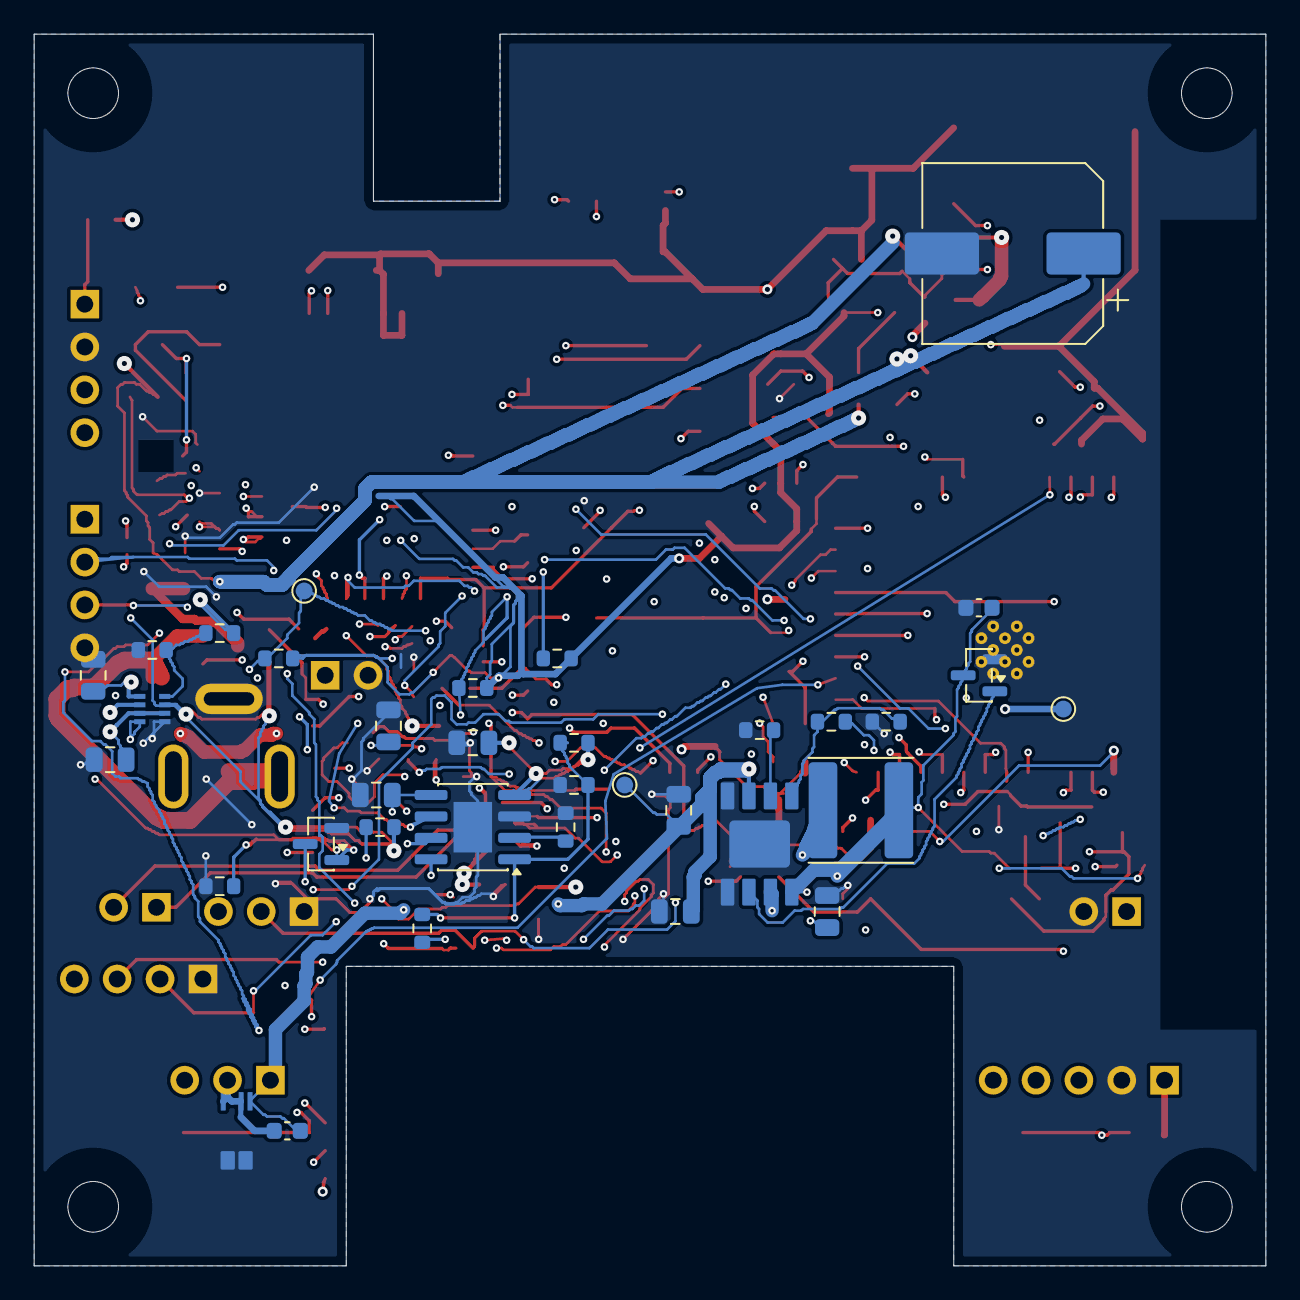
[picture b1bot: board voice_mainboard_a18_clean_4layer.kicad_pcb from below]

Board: 4 copper layers, 73.0 x 73.0 mm, 150 parts (35 on the bottom side), 87 nets.

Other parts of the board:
H1, H2, H3, H4: M3; A18_MountingHole_3mm_7mmReserve

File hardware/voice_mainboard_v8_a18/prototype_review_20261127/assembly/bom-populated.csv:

Comment,Designator,Footprint,Quantity,LCSC Part #,Manufacturer Part
0R NTC LINK,R67,Resistor_SMD:R_0603_1608Metric,1,,0R NTC LINK
0R RF SERIES,R13,Resistor_SMD:R_0603_1608Metric,1,,RC0603JR070RL
0R USB SERVICE DM,R27,Resistor_SMD:R_0402_1005Metric,1,,RC0402JR070RL
0R USB SERVICE DP,R26,Resistor_SMD:R_0402_1005Metric,1,,RC0402JR070RL
0R VBUS FROM SERVICE,R30,Resistor_SMD:R_0603_1608Metric,1,,RC0603JR070RL
100k,"R32,R5,R69",Resistor_SMD:R_0603_1608Metric,3,,100k
100k,"R15,R16,R6,R8",Resistor_SMD:R_0603_1608Metric,4,,RC0603FR07100KL
100k 0.1% MODEM RH,R2,Resistor_SMD:R_0603_1608Metric,1,,100k 0.1% MODEM RH
100k 0.1% PR TOP,R70,Resistor_SMD:R_0603_1608Metric,1,,100k 0.1% PR TOP
100k 1%,"R18,R20",Resistor_SMD:R_0603_1608Metric,2,,RC0603FR07100KL
100k 1% RH ESP,R59,Resistor_SMD:R_0603_1608Metric,1,,100k 1% RH ESP
100n,"C11,C13,C14,C15,C16,C17,C18,C58,C62,C69,C70",Capacitor_SMD:C_0603_1608Metric,11,,100n
100n MIC,C26,Capacitor_SMD:C_0603_1608Metric,1,,100n MIC
100n RGB,C74,Capacitor_SMD:C_0603_1608Metric,1,,
10k,"R4,R68,R72,R73,R74",Resistor_SMD:R_0603_1608Metric,5,,10k
10k,"R12,R21",Resistor_SMD:R_0603_1608Metric,2,,RC0603FR0710KL
10k 0.1%,R62,Resistor_SMD:R_0603_1608Metric,1,,10k 0.1%
10k 1%,R19,Resistor_SMD:R_0603_1608Metric,1,,RC0603FR0710KL
10k BOOT,R14,Resistor_SMD:R_0603_1608Metric,1,,10k BOOT
10k EN,R57,Resistor_SMD:R_0603_1608Metric,1,,10k EN
10u,C61,Capacitor_SMD:C_0805_2012Metric,1,,10u
10u 10V,C10,Capacitor_SMD:C_0805_2012Metric,1,,10u 10V
10u 10V X5R,"C67,C68",Capacitor_SMD:C_0805_2012Metric,2,,10u 10V X5R
12k 1%,R64,Resistor_SMD:R_0603_1608Metric,1,,12k 1%
150k 1%,R17,Resistor_SMD:R_0603_1608Metric,1,,RC0603FR07150KL
18.7k 0.1% MODEM RL,R3,Resistor_SMD:R_0603_1608Metric,1,,18.7k 0.1% MODEM RL
1S CELL + / - / NTC,J23,Connector_PinHeader_2.54mm:PinHeader_1x03_P2.54mm_Vertical,1,,1S CELL + / - / NTC
1u EN delay,C56,Capacitor_SMD:C_0603_1608Metric,1,,1u EN delay
200k 1%,R66,Resistor_SMD:R_0603_1608Metric,1,,200k 1%
22.1k 1% RL ESP,R60,Resistor_SMD:R_0603_1608Metric,1,,22.1k 1% RL ESP
220u 6.3V APAQ6R3AVEA221M0645,"C75,C76",Capacitor_SMD:CP_Elec_6.3x4.5,2,C176322,6R3AVEA221M0645
22R,"R10,R11,R9",Resistor_SMD:R_0603_1608Metric,3,,RC0603FR0722RL
22p ESP CFF,C63,Capacitor_SMD:C_0603_1608Metric,1,,22p ESP CFF
22p MODEM CFF,C37,Capacitor_SMD:C_0603_1608Metric,1,,22p MODEM CFF
22u,C57,Capacitor_SMD:C_0805_2012Metric,1,,22u
22u 10V X5R,"C64,C65,C66,C71,C72,C73",Capacitor_SMD:C_0805_2012Metric,6,,22u 10V X5R
22u 16V,"C4,C59,C6,C60,C7",Capacitor_SMD:C_0805_2012Metric,5,,22u 16V
2N7002K-7,Q7,Package_TO_SOT_SMD:SOT-23,1,,2N7002K-7
2N7002K-7 C85047,"Q1,Q2,Q4,Q5",Package_TO_SOT_SMD:SOT-23,4,C85047,2N7002K-7
30k 1% ISET,R63,Resistor_SMD:R_0603_1608Metric,1,,30k 1% ISET
33.2k 0.1% PR BOTTOM,R71,Resistor_SMD:R_0603_1608Metric,1,,33.2k 0.1% PR BOTTOM
330R RGB DIN,R77,Resistor_SMD:R_0603_1608Metric,1,,
33p,C12,Capacitor_SMD:C_0603_1608Metric,1,,33p
6.19k 1% NTC TOP,R65,Resistor_SMD:R_0603_1608Metric,1,,6.19k 1% NTC TOP
73.2k 0.1%,R61,Resistor_SMD:R_0603_1608Metric,1,,73.2k 0.1%
ASMD1812-400-16V C55014590,F1,Fuse:Fuse_1812_4532Metric,1,C55014590,ASMD1812-400-16V
"BSS84,215 C493579",Q3,Package_TO_SOT_SMD:SOT-23,1,C493579,"BSS84,215"
CL10B103KB8NNNC,"C19,C29",Capacitor_SMD:C_0603_1608Metric,2,C1589,CL10B103KB8NNNC
CL10B104KB8NNNC C1591,"C20,C28",Capacitor_SMD:C_0603_1608Metric,2,C1591,CL10B104KB8NNNC
DMP2035U-7 C110499,Q6,Package_TO_SOT_SMD:SOT-23,1,C110499,DMP2035U-7
ESP32-S3-WROOM-1-N8R8,U7,VoiceV2:V6_U7_SMD_LAND_MATCH,1,,ESP32-S3-WROOM-1-N8R8
ETA1096E8A,U15,VoiceV2:ETA1096_ESOP8,1,C7435200,ETA1096E8A
EXTERNAL CALL BUTTON,J17,Connector_PinHeader_2.54mm:PinHeader_1x02_P2.54mm_Vertical,1,,EXTERNAL CALL BUTTON
HX DC005-2.5-T 3A C18357600,J1,VoiceV2:HX_DC005_2p5_T,1,C18357600,HX DC005-2.5-T
INMP441 MODULE 3V3 GND BCLK WS SD,J14,Connector_PinHeader_2.54mm:PinHeader_1x05_P2.54mm_Vertical,1,,INMP441 MODULE 3V3 GND BCLK WS SD
JAE SF72S006 SIM CANDIDATE,J10,Connector_JAE:JAE_SIM_Card_SF72S006,1,C2977286,SF72S006VBD
LTE ANT U.FL,J11,VoiceV2:UFL_Hirose_2Layer_A18,1,C88374,U.FL-R-SMT-1(80)
MAX98357AETE+,U14,VoiceV2:V6_U14_SMD_LAND_MATCH,1,,MAX98357AETE+
ME2807A30M3G,U19,Package_TO_SOT_SMD:SOT-23,1,C236756,ME2807A30M3G
ML307C-DL,U1,VoiceV2:ML307C_DL_109_LIBRARY_REVIEW,1,C48972417,ML307C-DL
OCV471M1ATR-1010 470u 10V,C8,Capacitor_SMD:CP_Elec_10x10.5,1,C250035,OCV471M1ATR-1010
OPTIONAL RADAR 5V GND RX6 TX8,J16,Connector_PinHeader_2.54mm:PinHeader_1x04_P2.54mm_Vertical,1,,OPTIONAL RADAR 5V GND RX6 TX8
SN74LVC1T45DBVR,"U3,U4,U5",Package_TO_SOT_SMD:SOT-23-6,3,,SN74LVC1T45DBVR
SPEAKER BTL + / - NEVER GND,J15,Connector_PinHeader_2.54mm:PinHeader_1x02_P2.54mm_Vertical,1,,SPEAKER BTL + / - NEVER GND
SRV05-4 MSKSEMI,D1,Package_TO_SOT_SMD:SOT-23-6,1,,SRV05-4
SWPA4030S2R2NT 2.2uH +/-30%,L5,Inductor_SMD:L_Sunlord_SWPA4030S,1,,SWPA4030S2R2NT
SWPA6045S2R2MT,L4,Inductor_SMD:L_Sunlord_SWPA6045S,1,C83455,SWPA6045S2R2MT
SWPA6045S2R2MT C83455,L1,Inductor_SMD:L_Sunlord_SWPA6045S,1,C83455,SWPA6045S2R2MT
SY8089A1AAC,"U13,U2",Package_TO_SOT_SMD:SOT-23-5,2,,SY8089A1AAC
TACT 4.5x4.5 SMD,"SW1,SW2,SW3",Button_Switch_SMD:SW_SPST_TL3342,3,,TACT 4.5x4.5 SMD
TP4056-MS,U16,Package_SO:SOIC-8-1EP_3.9x4.9mm_P1.27mm_EP2.29x3mm,1,C7473158,TP4056-MS
TPS2117DRLR,U18,VoiceV2:TI_DRL0008A,1,C22399676,TPS2117DRLR
TTL GND TX43 RX44 5V,J18,Connector_PinHeader_2.54mm:PinHeader_1x04_P2.54mm_Vertical,1,,TTL GND TX43 RX44 5V
WS2812B-2020-V6,D2,LED_SMD:LED_WS2812B-2020_PLCC4_2.0x2.0mm,1,C52917434,WS2812B-2020-V6
XB7608AJL,U17,VoiceV2:XB7608_CPC5,1,C2980178,XB7608AJL
